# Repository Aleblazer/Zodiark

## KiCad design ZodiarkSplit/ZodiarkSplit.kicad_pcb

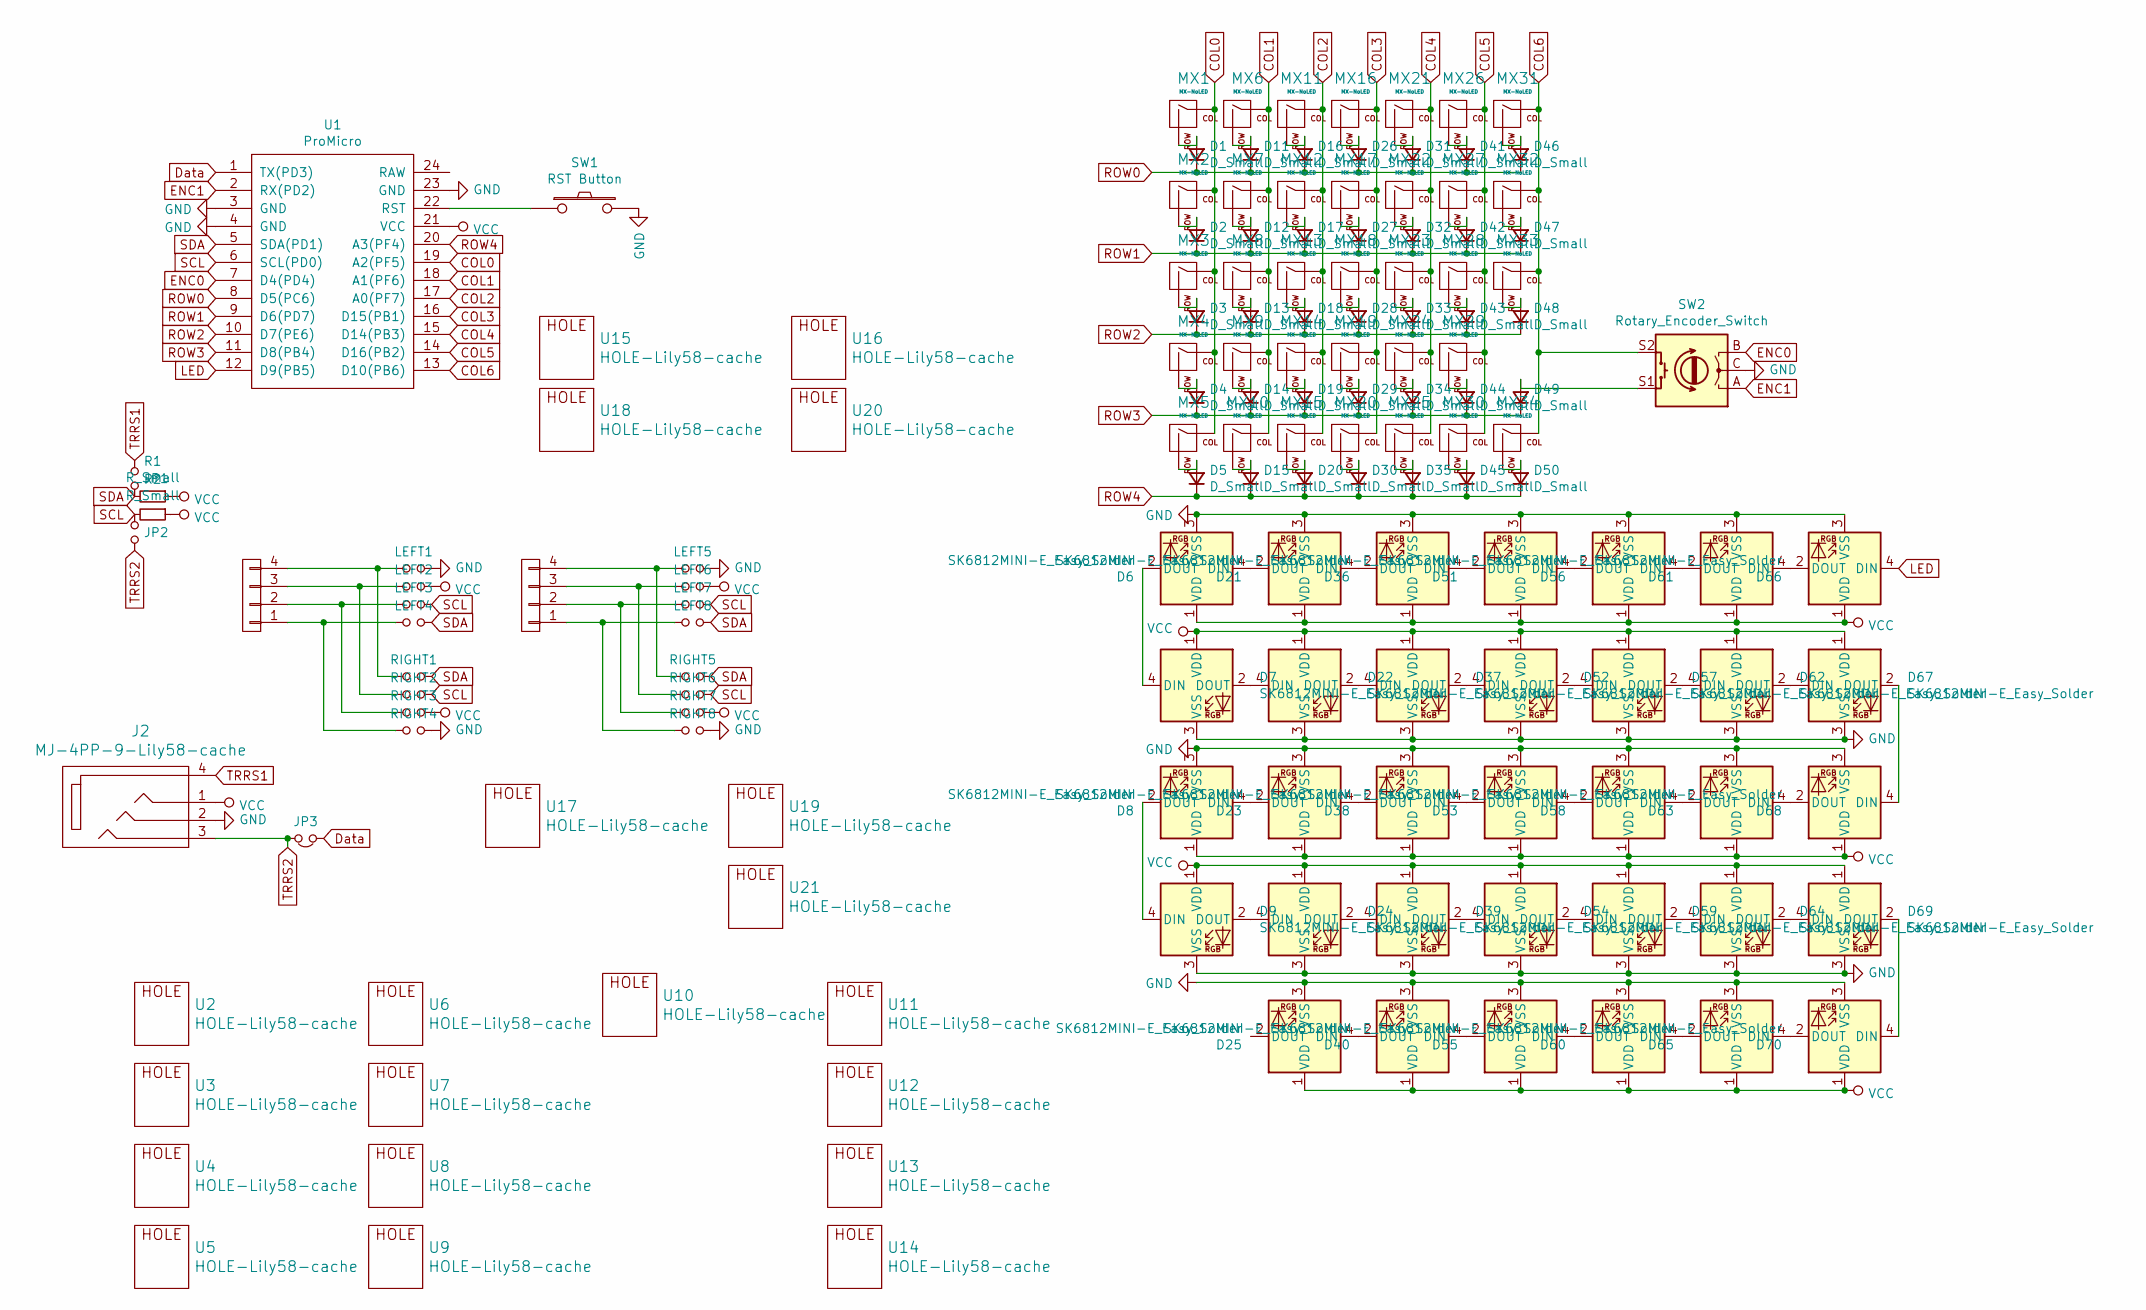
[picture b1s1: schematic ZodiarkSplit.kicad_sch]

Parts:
D1, D2, D3, D4, D5, D11, D12, D13, D14, D15, D16, D17, D18, D19, D20, D26, D27, D28, D29, D30, D31, D32, D33, D34, D35, D41, D42, D43, D44, D45, D46, D47, D48, D49, D50: D_Small; D_SOD123F
D6, D7, D8, D9, D21, D22, D23, D24, D25, D36, D37, D38, D39, D40, D51, D52, D53, D54, D55, D56, D57, D58, D59, D60, D61, D62, D63, D64, D65, D66, D67, D68, D69, D70: SK6812MINI-E_Easy_Solder; YS-SK6812MINI-E
J2: MJ-4PP-9-Lily58-cache; MJ-4PP-9_rev2
JP1, JP2: JP1; jumper_smd_2dub
JP3: Jumper_NC_Small; jumper_data
LEFT1, LEFT2, LEFT3, LEFT4, LEFT5, LEFT6, LEFT7, LEFT8: JP1; Jumper
MX1, MX2, MX3, MX4, MX5, MX6, MX7, MX8, MX9, MX10, MX11, MX12, MX13, MX14, MX15, MX16, MX17, MX18, MX19, MX20, MX21, MX22, MX23, MX24, MX25, MX26, MX27, MX28, MX29, MX30, MX31, MX32, MX33, MX34: MX-NoLED; MXOnly-1U-Hotswap-Double-noled
P1, P2: OLED; OLED_4Pin
R1, R2: R_Small; RESISTOR_mini
RIGHT1, RIGHT2, RIGHT3, RIGHT4, RIGHT5, RIGHT6, RIGHT7, RIGHT8: JP1; Jumper
SW1: RST Button; TACT_SWITCH_TVBP06
SW2: Rotary_Encoder_Switch; RotaryEncoder_EC11
U1: ProMicro; ProMicro_rev2
U2, U3, U4, U5, U6, U7, U8, U9, U10, U11, U12, U13, U14: HOLE-Lily58-cache; HOLE_M2_TH
U15, U16, U17, U18, U19, U20, U21: HOLE-Lily58-cache; HOLE_M2

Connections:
COL0: MX1.1 (COL), MX2.1 (COL), MX3.1 (COL), MX4.1 (COL), MX5.1 (COL), U1.19 (A2(PF5))
COL1: MX6.1 (COL), MX7.1 (COL), MX8.1 (COL), MX9.1 (COL), MX10.1 (COL), U1.18 (A1(PF6))
COL2: MX11.1 (COL), MX12.1 (COL), MX13.1 (COL), MX14.1 (COL), MX15.1 (COL), U1.17 (A0(PF7))
COL3: MX16.1 (COL), MX17.1 (COL), MX18.1 (COL), MX19.1 (COL), MX20.1 (COL), U1.16 (D15(PB1))
COL4: MX21.1 (COL), MX22.1 (COL), MX23.1 (COL), MX24.1 (COL), MX25.1 (COL), U1.15 (D14(PB3))
COL5: MX26.1 (COL), MX27.1 (COL), MX28.1 (COL), MX29.1 (COL), MX30.1 (COL), U1.14 (D16(PB2))
COL6: MX31.1 (COL), MX32.1 (COL), MX33.1 (COL), MX34.1 (COL), SW2.S2, U1.13 (D10(PB6))
Data: JP3.1, U1.1 (TX(PD3))
ENC0: SW2.B, U1.7 (D4(PD4))
ENC1: SW2.A, U1.2 (RX(PD2))
GND: D6.3 (VSS), D7.3 (VSS), D8.3 (VSS), D9.3 (VSS), D21.3 (VSS), D22.3 (VSS), D23.3 (VSS), D24.3 (VSS), D25.3 (VSS), D36.3 (VSS), D37.3 (VSS), D38.3 (VSS), D39.3 (VSS), D40.3 (VSS), D51.3 (VSS), D52.3 (VSS), D53.3 (VSS), D54.3 (VSS), D55.3 (VSS), D56.3 (VSS), D57.3 (VSS), D58.3 (VSS), D59.3 (VSS), D60.3 (VSS), D61.3 (VSS), D62.3 (VSS), D63.3 (VSS), D64.3 (VSS), D65.3 (VSS), D66.3 (VSS), D67.3 (VSS), D68.3 (VSS), D69.3 (VSS), D70.3 (VSS), J2.2, LEFT1.2, LEFT5.2, RIGHT4.2, RIGHT8.2, SW1.2, SW2.C, U1.3 (GND), U1.4 (GND), U1.23 (GND)
LED: D66.4 (DIN), U1.12 (D9(PB5))
unnamed: D1.2 (A), MX1.2 (ROW)
unnamed: D2.2 (A), MX2.2 (ROW)
unnamed: D3.2 (A), MX3.2 (ROW)
unnamed: D4.2 (A), MX4.2 (ROW)
unnamed: D5.2 (A), MX5.2 (ROW)
unnamed: D6.2 (DOUT), D7.4 (DIN)
unnamed: D8.2 (DOUT), D9.4 (DIN)
unnamed: D11.2 (A), MX6.2 (ROW)
unnamed: D12.2 (A), MX7.2 (ROW)
unnamed: D13.2 (A), MX8.2 (ROW)
unnamed: D14.2 (A), MX9.2 (ROW)
unnamed: D15.2 (A), MX10.2 (ROW)
unnamed: D16.2 (A), MX11.2 (ROW)
unnamed: D17.2 (A), MX12.2 (ROW)
unnamed: D18.2 (A), MX13.2 (ROW)
unnamed: D19.2 (A), MX14.2 (ROW)
unnamed: D20.2 (A), MX15.2 (ROW)
unnamed: D6.4 (DIN), D21.2 (DOUT)
unnamed: D21.4 (DIN), D36.2 (DOUT)
unnamed: D22.2 (DOUT), D37.4 (DIN)
unnamed: D7.2 (DOUT), D22.4 (DIN)
unnamed: D8.4 (DIN), D23.2 (DOUT)
unnamed: D23.4 (DIN), D38.2 (DOUT)
unnamed: D24.2 (DOUT), D39.4 (DIN)
unnamed: D9.2 (DOUT), D24.4 (DIN)
unnamed: D25.4 (DIN), D40.2 (DOUT)
unnamed: D26.2 (A), MX16.2 (ROW)
unnamed: D27.2 (A), MX17.2 (ROW)
unnamed: D28.2 (A), MX18.2 (ROW)
unnamed: D29.2 (A), MX19.2 (ROW)
unnamed: D30.2 (A), MX20.2 (ROW)
unnamed: D31.2 (A), MX21.2 (ROW)
unnamed: D32.2 (A), MX22.2 (ROW)
unnamed: D33.2 (A), MX23.2 (ROW)
unnamed: D34.2 (A), MX24.2 (ROW)
unnamed: D35.2 (A), MX25.2 (ROW)
unnamed: D36.4 (DIN), D51.2 (DOUT)
unnamed: D37.2 (DOUT), D52.4 (DIN)
unnamed: D38.4 (DIN), D53.2 (DOUT)
unnamed: D39.2 (DOUT), D54.4 (DIN)
unnamed: D40.4 (DIN), D55.2 (DOUT)
unnamed: D41.2 (A), MX26.2 (ROW)
unnamed: D42.2 (A), MX27.2 (ROW)
unnamed: D43.2 (A), MX28.2 (ROW)
unnamed: D44.2 (A), MX29.2 (ROW)
unnamed: D45.2 (A), MX30.2 (ROW)
unnamed: D46.2 (A), MX31.2 (ROW)
unnamed: D47.2 (A), MX32.2 (ROW)
unnamed: D48.2 (A), MX33.2 (ROW)
unnamed: D49.2 (A), SW2.S1
unnamed: D50.2 (A), MX34.2 (ROW)
unnamed: D51.4 (DIN), D56.2 (DOUT)
unnamed: D52.2 (DOUT), D57.4 (DIN)
unnamed: D53.4 (DIN), D58.2 (DOUT)
unnamed: D54.2 (DOUT), D59.4 (DIN)
unnamed: D55.4 (DIN), D60.2 (DOUT)
unnamed: D56.4 (DIN), D61.2 (DOUT)
unnamed: D57.2 (DOUT), D62.4 (DIN)
unnamed: D58.4 (DIN), D63.2 (DOUT)
unnamed: D59.2 (DOUT), D64.4 (DIN)
unnamed: D60.4 (DIN), D65.2 (DOUT)
unnamed: D61.4 (DIN), D66.2 (DOUT)
unnamed: D62.2 (DOUT), D67.4 (DIN)
unnamed: D63.4 (DIN), D68.2 (DOUT)
unnamed: D64.2 (DOUT), D69.4 (DIN)
unnamed: D65.4 (DIN), D70.2 (DOUT)
unnamed: D67.2 (DOUT), D68.4 (DIN)
unnamed: D69.2 (DOUT), D70.4 (DIN)
unnamed: LEFT1.1, P1.4, RIGHT1.1
unnamed: LEFT2.1, P1.3, RIGHT2.1
unnamed: LEFT3.1, P1.2, RIGHT3.1
unnamed: LEFT4.1, P1.1, RIGHT4.1
unnamed: LEFT5.1, P2.4, RIGHT5.1
unnamed: LEFT6.1, P2.3, RIGHT6.1
unnamed: LEFT7.1, P2.2, RIGHT7.1
unnamed: LEFT8.1, P2.1, RIGHT8.1
unnamed: SW1.1, U1.22 (RST)
ROW0: D1.1 (K), D11.1 (K), D16.1 (K), D26.1 (K), D31.1 (K), D41.1 (K), D46.1 (K), U1.8 (D5(PC6))
ROW1: D2.1 (K), D12.1 (K), D17.1 (K), D27.1 (K), D32.1 (K), D42.1 (K), D47.1 (K), U1.9 (D6(PD7))
ROW2: D3.1 (K), D13.1 (K), D18.1 (K), D28.1 (K), D33.1 (K), D43.1 (K), D48.1 (K), U1.10 (D7(PE6))
ROW3: D4.1 (K), D14.1 (K), D19.1 (K), D29.1 (K), D34.1 (K), D44.1 (K), D49.1 (K), U1.11 (D8(PB4))
ROW4: D5.1 (K), D15.1 (K), D20.1 (K), D30.1 (K), D35.1 (K), D45.1 (K), D50.1 (K), U1.20 (A3(PF4))
SCL: JP2.1, LEFT3.2, LEFT7.2, R2.2, RIGHT2.2, RIGHT6.2, U1.6 (SCL(PD0))
SDA: JP1.2, LEFT4.2, LEFT8.2, R1.2, RIGHT1.2, RIGHT5.2, U1.5 (SDA(PD1))
TRRS1: J2.4, JP1.1
TRRS2: J2.3, JP2.2, JP3.2
VCC: D6.1 (VDD), D7.1 (VDD), D8.1 (VDD), D9.1 (VDD), D21.1 (VDD), D22.1 (VDD), D23.1 (VDD), D24.1 (VDD), D25.1 (VDD), D36.1 (VDD), D37.1 (VDD), D38.1 (VDD), D39.1 (VDD), D40.1 (VDD), D51.1 (VDD), D52.1 (VDD), D53.1 (VDD), D54.1 (VDD), D55.1 (VDD), D56.1 (VDD), D57.1 (VDD), D58.1 (VDD), D59.1 (VDD), D60.1 (VDD), D61.1 (VDD), D62.1 (VDD), D63.1 (VDD), D64.1 (VDD), D65.1 (VDD), D66.1 (VDD), D67.1 (VDD), D68.1 (VDD), D69.1 (VDD), D70.1 (VDD), J2.1, LEFT2.2, LEFT6.2, R1.1, R2.1, RIGHT3.2, RIGHT7.2, U1.21 (VCC)

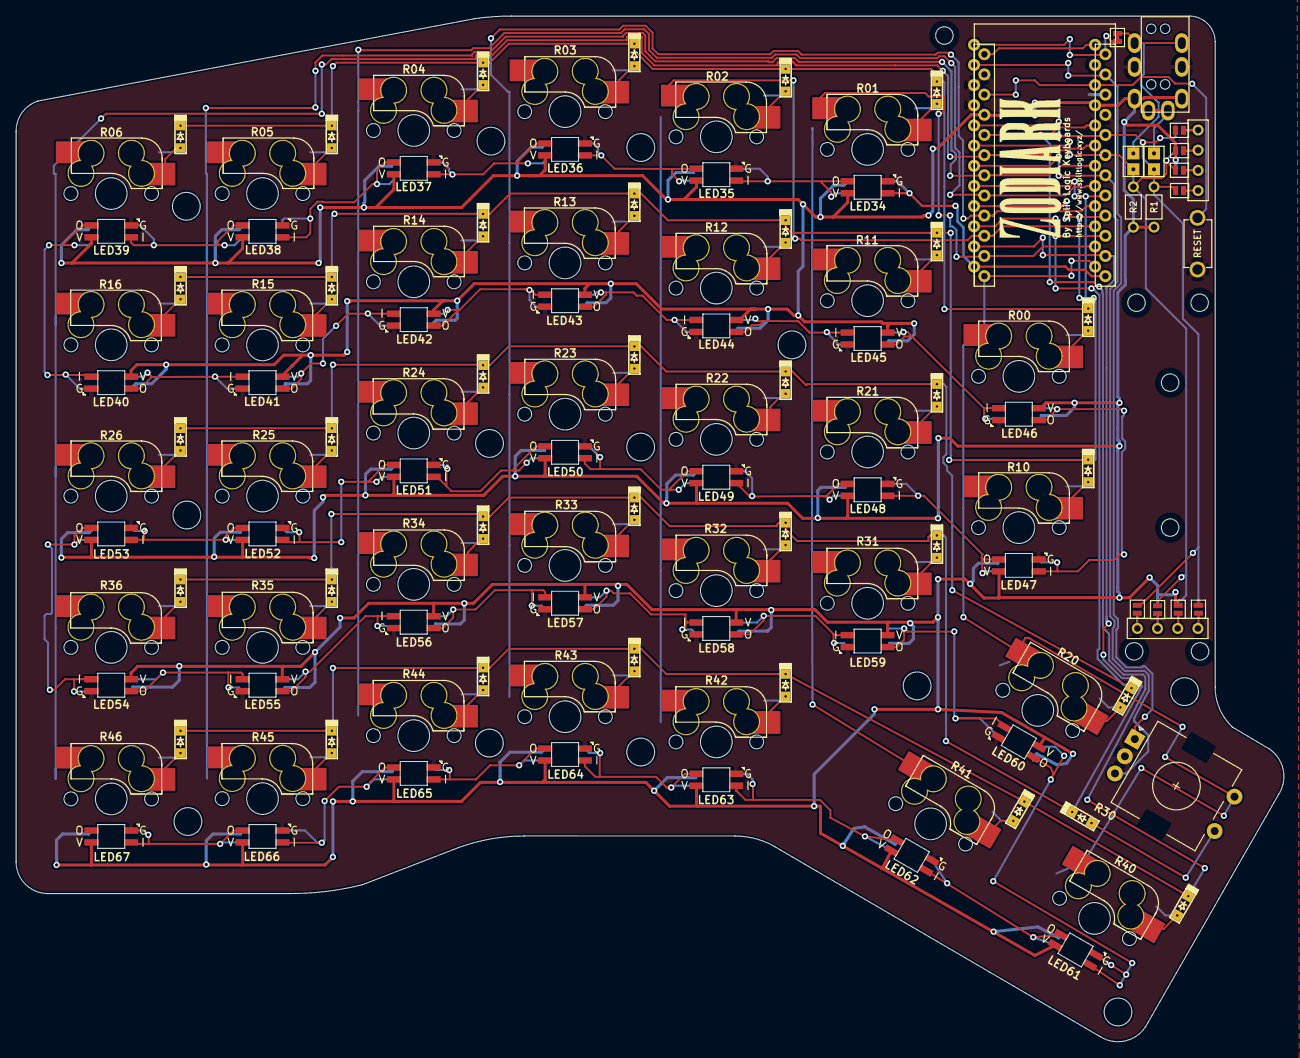
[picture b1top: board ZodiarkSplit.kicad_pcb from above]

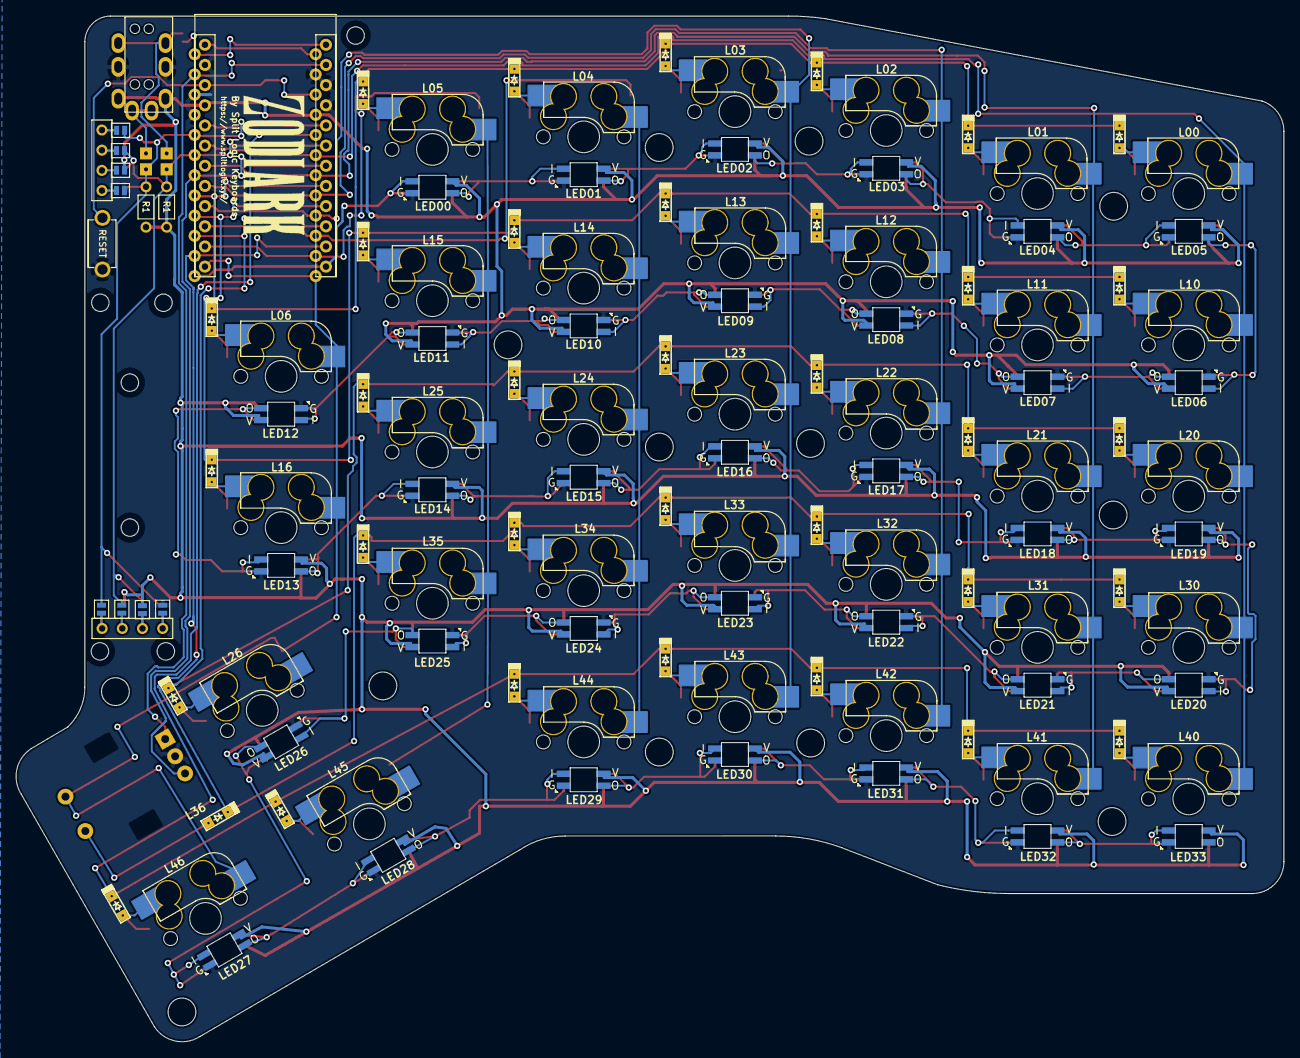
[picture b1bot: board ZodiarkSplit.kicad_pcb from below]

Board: 2 copper layers, 159.6 x 129.1 mm, 150 parts (8 on the bottom side), 99 nets.

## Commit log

2020-12-11 Adding QMK firmware folder
2021-02-01 Final Proto
2023-04-04 Clean-up
2023-04-04 License Update
    Updated to the MIT license and credited all parties.
2023-04-04 Clean-Up Pt.2
    Zodiark Clean-Up
2024-05-26 Final Cleanup
    Final Cleanup for public release.
